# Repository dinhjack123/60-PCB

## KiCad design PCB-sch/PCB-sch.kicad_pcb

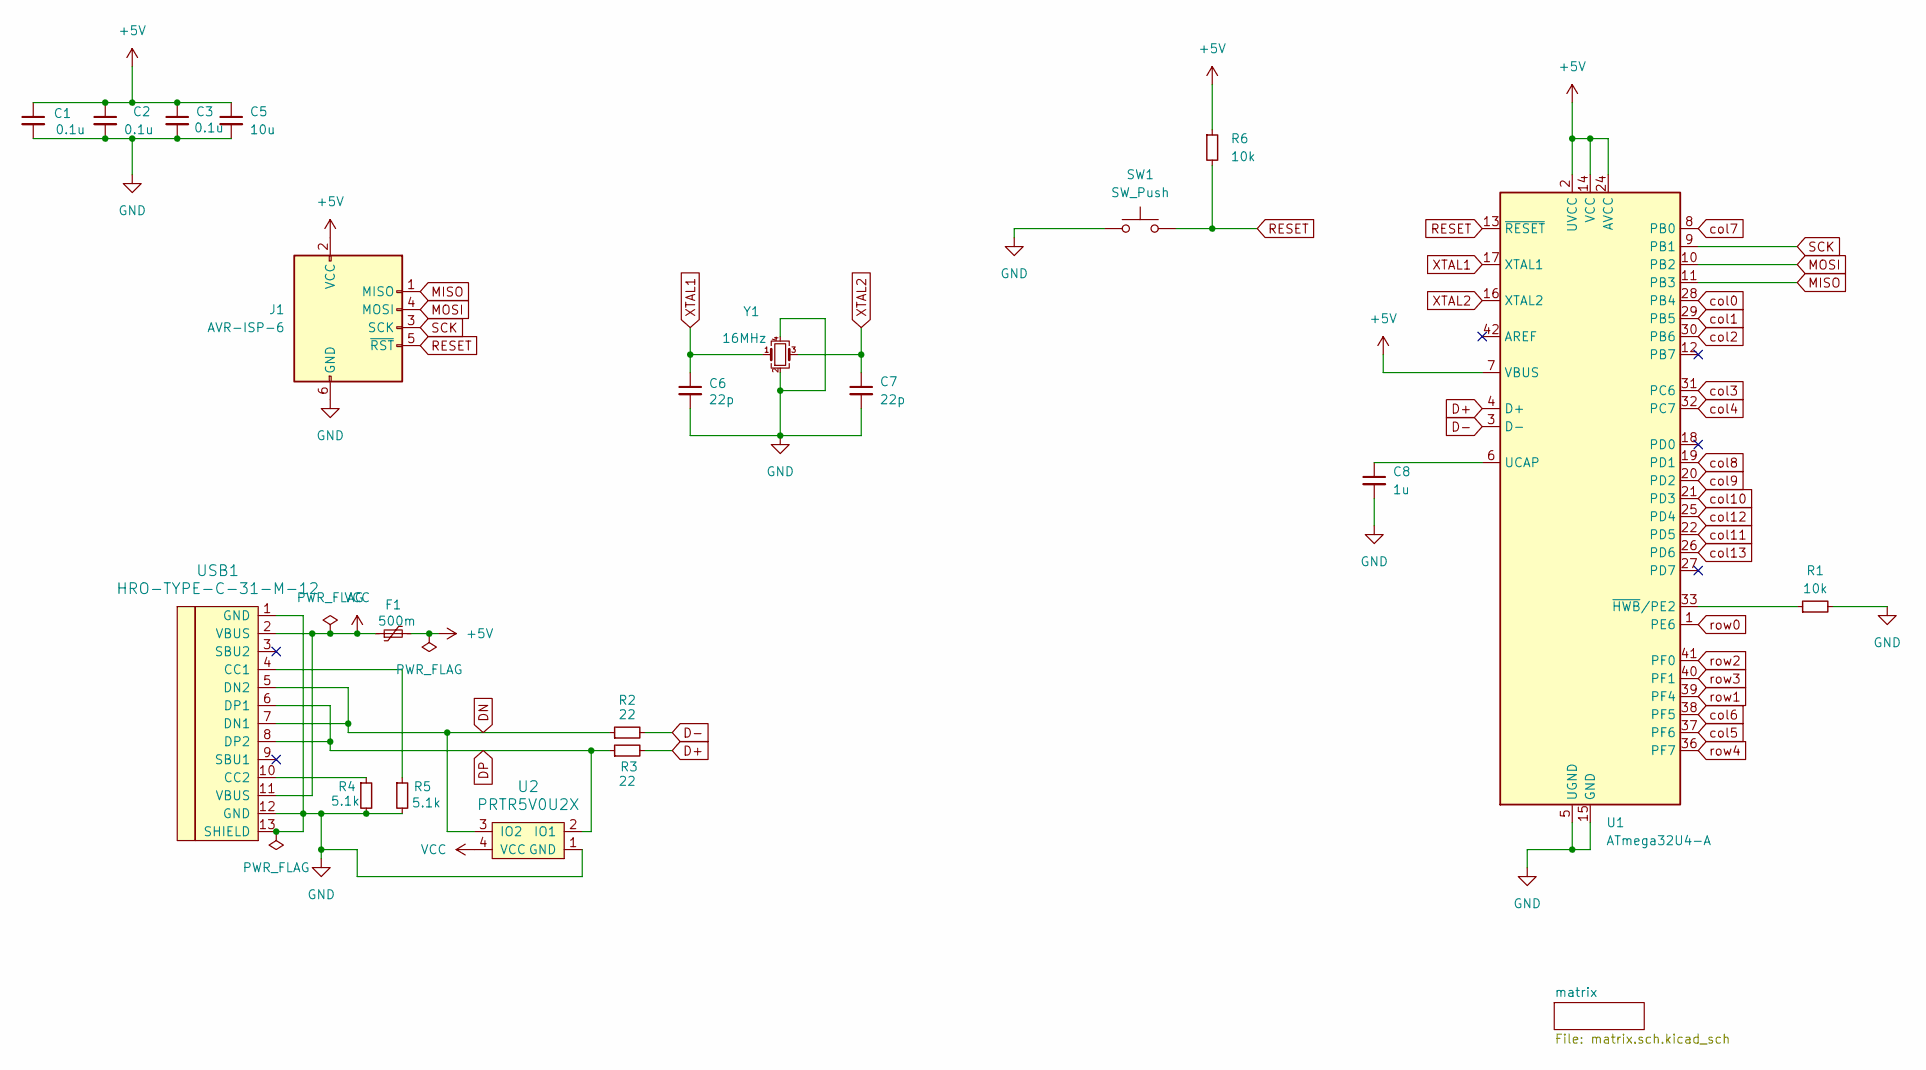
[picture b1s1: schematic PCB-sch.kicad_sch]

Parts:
C1, C2, C3: 0.1u; C_0805_2012Metric_Pad1.18x1.45mm_HandSolder
C5: 10u; C_0805_2012Metric_Pad1.18x1.45mm_HandSolder
C6, C7: 22p; C_0805_2012Metric_Pad1.18x1.45mm_HandSolder
C8: 1u; C_0805_2012Metric_Pad1.18x1.45mm_HandSolder
F1: 500m; Fuse_1206_3216Metric_Pad1.42x1.75mm_HandSolder
J1: AVR-ISP-6; Reset_Pretty-Mask
R1, R6: 10k; R_0805_2012Metric_Pad1.20x1.40mm_HandSolder
R2, R3: 22; R_0805_2012Metric_Pad1.20x1.40mm_HandSolder
R4, R5: 5.1k; R_0805_2012Metric_Pad1.20x1.40mm_HandSolder
SW1: SW_Push; SW_SPST_SKQG_WithStem
U1: ATmega32U4-A; TQFP-44_10x10mm_P0.8mm
U2: PRTR5V0U2X; SOT143B
USB1: HRO-TYPE-C-31-M-12; HRO-TYPE-C-31-M-12-HandSoldering
Y1: 16MHz; Crystal_SMD_3225-4Pin_3.2x2.5mm_HandSoldering

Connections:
+5V: C1.1, C2.1, C3.1, C5.1, F1.2, J1.2 (VCC), R6.1, U1.2 (UVCC), U1.7 (VBUS), U1.14 (VCC), U1.24 (AVCC), U1.34 (VCC), U1.44 (AVCC)
D+: R3.2, U1.4 (D+)
D-: R2.2, U1.3 (D-)
DN: R2.1, U2.3 (IO2), USB1.5 (DN2), USB1.7 (DN1)
DP: R3.1, U2.2 (IO1), USB1.6 (DP1), USB1.8 (DP2)
GND: C1.2, C2.2, C3.2, C5.2, C6.2, C7.2, C8.2, J1.6 (GND), R1.2, R4.2, R5.2, SW1.1, U1.5 (UGND), U1.15 (GND), U1.23 (GND), U1.35 (GND), U1.43 (GND), U2.1 (GND), USB1.1 (GND), USB1.12 (GND), USB1.13 (SHIELD), Y1.2, Y1.4
MISO: J1.1 (MISO), U1.11 (PB3)
MOSI: J1.4 (MOSI), U1.10 (PB2)
unnamed: C8.1, U1.6 (UCAP)
unnamed: R1.1, U1.33 (~HWB/PE2)
unnamed: R5.1, USB1.4 (CC1)
unnamed: R4.1, USB1.10 (CC2)
RESET: J1.5 (~RST), R6.2, SW1.2, U1.13 (~RESET)
SCK: J1.3 (SCK), U1.9 (PB1)
VCC: F1.1, U2.4 (VCC), USB1.2 (VBUS), USB1.11 (VBUS)
XTAL1: C6.1, U1.17 (XTAL1), Y1.1
XTAL2: C7.1, U1.16 (XTAL2), Y1.3
col0: U1.28 (PB4); also elsewhere on the board
col1: U1.29 (PB5); also elsewhere on the board
col2: U1.30 (PB6); also elsewhere on the board
col3: U1.31 (PC6); also elsewhere on the board
col4: U1.32 (PC7); also elsewhere on the board
col5: U1.37 (PF6); also elsewhere on the board
col6: U1.38 (PF5); also elsewhere on the board
col7: U1.8 (PB0); also elsewhere on the board
col8: U1.19 (PD1); also elsewhere on the board
col9: U1.20 (PD2); also elsewhere on the board
col10: U1.21 (PD3); also elsewhere on the board
col11: U1.22 (PD5); also elsewhere on the board
col12: U1.25 (PD4); also elsewhere on the board
col13: U1.26 (PD6); also elsewhere on the board
row0: U1.1 (PE6); also elsewhere on the board
row1: U1.39 (PF4); also elsewhere on the board
row2: U1.41 (PF0); also elsewhere on the board
row3: U1.40 (PF1); also elsewhere on the board
row4: U1.36 (PF7); also elsewhere on the board

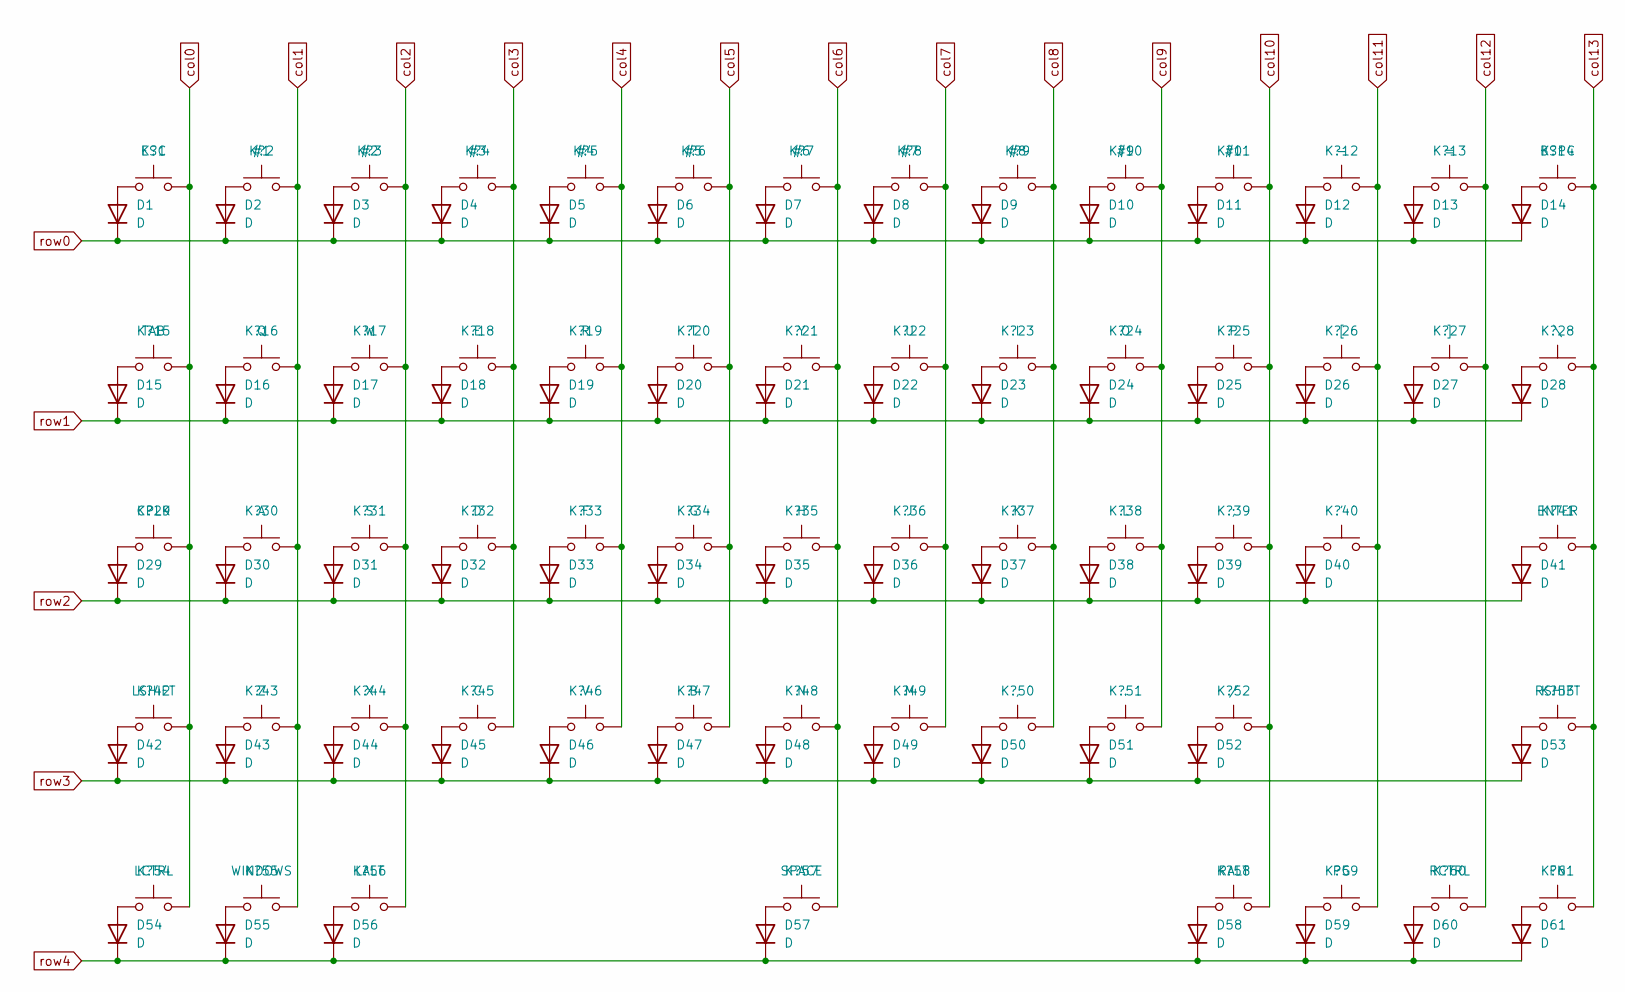
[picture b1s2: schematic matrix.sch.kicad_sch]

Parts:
D1, D2, D3, D4, D5, D6, D7, D8, D9, D10, D11, D12, D13, D14, D15, D16, D17, D18, D19, D20, D21, D22, D23, D24, D25, D26, D27, D28, D29, D30, D31, D32, D33, D34, D35, D36, D37, D38, D39, D40, D41, D42, D43, D44, D45, D46, D47, D48, D49, D50, D51, D52, D53, D54, D55, D56, D57, D58, D59, D60, D61: D; D_SOD-123
K?1: ESC; MX-Hotswap-1U
K?2: #1; MX-Hotswap-1U
K?3: #2; MX-Hotswap-1U
K?4: #3; MX-Hotswap-1U
K?5: #4; MX-Hotswap-1U
K?6: #5; MX-Hotswap-1U
K?7: #6; MX-Hotswap-1U
K?8: #7; MX-Hotswap-1U
K?9: #8; MX-Hotswap-1U
K?10: #9; MX-Hotswap-1U
K?11: #0; MX-Hotswap-1U
K?12: -; MX-Hotswap-1U
K?13: =; MX-Hotswap-1U
K?14: BSPC; MX-Hotswap-2U
K?15: TAB; MX-Hotswap-1.5U
K?16: Q; MX-Hotswap-1U
K?17: W; MX-Hotswap-1U
K?18: E; MX-Hotswap-1U
K?19: R; MX-Hotswap-1U
K?20: T; MX-Hotswap-1U
K?21: Y; MX-Hotswap-1U
K?22: U; MX-Hotswap-1U
K?23: I; MX-Hotswap-1U
K?24: O; MX-Hotswap-1U
K?25: P; MX-Hotswap-1U
K?26: [; MX-Hotswap-1U
K?27: ]; MX-Hotswap-1U
K?28: \; MX-Hotswap-1.5U
K?29: CPLK; MX-Hotswap-1.75U
K?30: A; MX-Hotswap-1U
K?31: S; MX-Hotswap-1U
K?32: D; MX-Hotswap-1U
K?33: F; MX-Hotswap-1U
K?34: G; MX-Hotswap-1U
K?35: H; MX-Hotswap-1U
K?36: J; MX-Hotswap-1U
K?37: K; MX-Hotswap-1U
K?38: L; MX-Hotswap-1U
K?39: ;; MX-Hotswap-1U
K?40: '; MX-Hotswap-1U
K?41: ENTER; MX-Hotswap-2.25U
K?42: LSHIFT; MX-Hotswap-2.25U
K?43: Z; MX-Hotswap-1U
K?44: X; MX-Hotswap-1U
K?45: C; MX-Hotswap-1U
K?46: V; MX-Hotswap-1U
K?47: B; MX-Hotswap-1U
K?48: N; MX-Hotswap-1U
K?49: M; MX-Hotswap-1U
K?50: ,; MX-Hotswap-1U
K?51: .; MX-Hotswap-1U
K?52: /; MX-Hotswap-1U
K?53: RSHIFT; MX-Hotswap-2.75U
K?54: LCTRL; MX-Hotswap-1.25U
K?55: WINDOWS; MX-Hotswap-1.25U
K?56: LALT; MX-Hotswap-1.25U
K?57: SPACE; MX-Hotswap-6.25U-ReversedStabilizers
K?58: RALT; MX-Hotswap-1.25U
K?59: PG; MX-Hotswap-1.25U
K?60: RCTRL; MX-Hotswap-1.25U
K?61: FN; MX-Hotswap-1.25U

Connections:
unnamed: D1.2 (A), K?1.1
unnamed: D2.2 (A), K?2.1
unnamed: D3.2 (A), K?3.1
unnamed: D4.2 (A), K?4.1
unnamed: D5.2 (A), K?5.1
unnamed: D6.2 (A), K?6.1
unnamed: D7.2 (A), K?7.1
unnamed: D8.2 (A), K?8.1
unnamed: D9.2 (A), K?9.1
unnamed: D10.2 (A), K?10.1
unnamed: D11.2 (A), K?11.1
unnamed: D12.2 (A), K?12.1
unnamed: D13.2 (A), K?13.1
unnamed: D14.2 (A), K?14.1
unnamed: D15.2 (A), K?15.1
unnamed: D16.2 (A), K?16.1
unnamed: D17.2 (A), K?17.1
unnamed: D18.2 (A), K?18.1
unnamed: D19.2 (A), K?19.1
unnamed: D20.2 (A), K?20.1
unnamed: D21.2 (A), K?21.1
unnamed: D22.2 (A), K?22.1
unnamed: D23.2 (A), K?23.1
unnamed: D24.2 (A), K?24.1
unnamed: D25.2 (A), K?25.1
unnamed: D26.2 (A), K?26.1
unnamed: D27.2 (A), K?27.1
unnamed: D28.2 (A), K?28.1
unnamed: D29.2 (A), K?29.1
unnamed: D30.2 (A), K?30.1
unnamed: D31.2 (A), K?31.1
unnamed: D32.2 (A), K?32.1
unnamed: D33.2 (A), K?33.1
unnamed: D34.2 (A), K?34.1
unnamed: D35.2 (A), K?35.1
unnamed: D36.2 (A), K?36.1
unnamed: D37.2 (A), K?37.1
unnamed: D38.2 (A), K?38.1
unnamed: D39.2 (A), K?39.1
unnamed: D40.2 (A), K?40.1
unnamed: D41.2 (A), K?41.1
unnamed: D42.2 (A), K?42.1
unnamed: D43.2 (A), K?43.1
unnamed: D44.2 (A), K?44.1
unnamed: D45.2 (A), K?45.1
unnamed: D46.2 (A), K?46.1
unnamed: D47.2 (A), K?47.1
unnamed: D48.2 (A), K?48.1
unnamed: D49.2 (A), K?49.1
unnamed: D50.2 (A), K?50.1
unnamed: D51.2 (A), K?51.1
unnamed: D52.2 (A), K?52.1
unnamed: D53.2 (A), K?53.1
unnamed: D54.2 (A), K?54.1
unnamed: D55.2 (A), K?55.1
unnamed: D56.2 (A), K?56.1
unnamed: D57.2 (A), K?57.1
unnamed: D58.2 (A), K?58.1
unnamed: D59.2 (A), K?59.1
unnamed: D60.2 (A), K?60.1
unnamed: D61.2 (A), K?61.1
col0: K?1.2, K?15.2, K?29.2, K?42.2, K?54.2; also elsewhere on the board
col1: K?2.2, K?16.2, K?30.2, K?43.2, K?55.2; also elsewhere on the board
col2: K?3.2, K?17.2, K?31.2, K?44.2, K?56.2; also elsewhere on the board
col3: K?4.2, K?18.2, K?32.2, K?45.2; also elsewhere on the board
col4: K?5.2, K?19.2, K?33.2, K?46.2; also elsewhere on the board
col5: K?6.2, K?20.2, K?34.2, K?47.2; also elsewhere on the board
col6: K?7.2, K?21.2, K?35.2, K?48.2, K?57.2; also elsewhere on the board
col7: K?8.2, K?22.2, K?36.2, K?49.2; also elsewhere on the board
col8: K?9.2, K?23.2, K?37.2, K?50.2; also elsewhere on the board
col9: K?10.2, K?24.2, K?38.2, K?51.2; also elsewhere on the board
col10: K?11.2, K?25.2, K?39.2, K?52.2, K?58.2; also elsewhere on the board
col11: K?12.2, K?26.2, K?40.2, K?59.2; also elsewhere on the board
col12: K?13.2, K?27.2, K?60.2; also elsewhere on the board
col13: K?14.2, K?28.2, K?41.2, K?53.2, K?61.2; also elsewhere on the board
row0: D1.1 (K), D2.1 (K), D3.1 (K), D4.1 (K), D5.1 (K), D6.1 (K), D7.1 (K), D8.1 (K), D9.1 (K), D10.1 (K), D11.1 (K), D12.1 (K), D13.1 (K), D14.1 (K); also elsewhere on the board
row1: D15.1 (K), D16.1 (K), D17.1 (K), D18.1 (K), D19.1 (K), D20.1 (K), D21.1 (K), D22.1 (K), D23.1 (K), D24.1 (K), D25.1 (K), D26.1 (K), D27.1 (K), D28.1 (K); also elsewhere on the board
row2: D29.1 (K), D30.1 (K), D31.1 (K), D32.1 (K), D33.1 (K), D34.1 (K), D35.1 (K), D36.1 (K), D37.1 (K), D38.1 (K), D39.1 (K), D40.1 (K), D41.1 (K); also elsewhere on the board
row3: D42.1 (K), D43.1 (K), D44.1 (K), D45.1 (K), D46.1 (K), D47.1 (K), D48.1 (K), D49.1 (K), D50.1 (K), D51.1 (K), D52.1 (K), D53.1 (K); also elsewhere on the board
row4: D54.1 (K), D55.1 (K), D56.1 (K), D57.1 (K), D58.1 (K), D59.1 (K), D60.1 (K), D61.1 (K); also elsewhere on the board

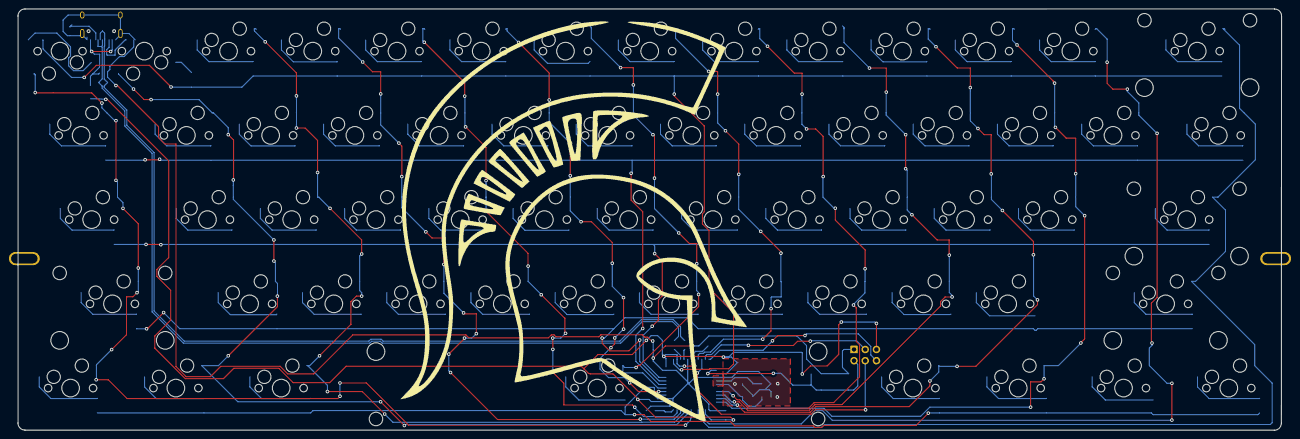
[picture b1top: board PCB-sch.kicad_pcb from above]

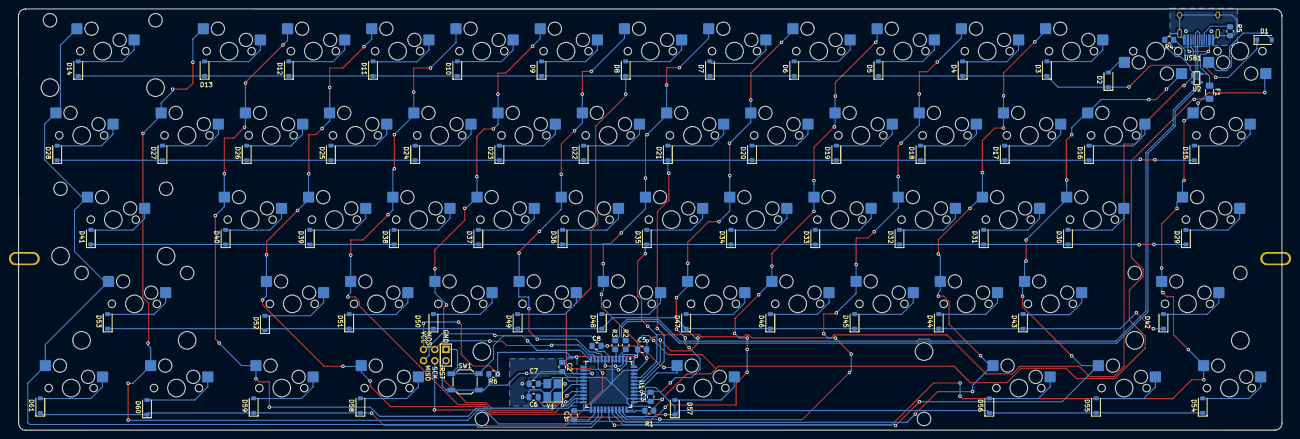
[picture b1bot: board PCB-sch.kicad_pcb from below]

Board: 2 copper layers, 285.8 x 95.3 mm, 142 parts (142 on the bottom side), 97 nets.

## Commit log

2024-12-15 test
2024-12-15 sub modules
2024-12-20 rerouted vias
2024-12-21 final edits
